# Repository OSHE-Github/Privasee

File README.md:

# Privasee

There are multiple different types of cameras. Detecting with them can be done in a combination of different ways. Some of these way include, but are not limited too detecting the infrared light pulses, reading the Radio Frequency and a handful of other waysPrivasee is a two semester project intended to locate and detect cameras. Additionally, the device itself aims to be low-cost, mobile, and efficient for detection. In other words, the device should be able to scan an area such as a hotel room and indicate to the user if there is a hidden camera. The basis of what to detect for hidden cameras boils down to infrared, radio frequencies, and possibly mac addresses. Infrared is a common trait of hidden cameras since this allows cameras to operate and record in low visibility. Radio frequency is used by hidden cameras to transmit data back to the owner. Mac addresses involve picking up packets sent in the area and displaying the signal strength and address of the device.

# Current State

The current prototype includes:
  
  - IR Detection
  - Mac Adress Reading 
  - RF detection (?)

  The system operates as a standalone or works with a laptop to detect cameras
  
# Features
## Infared Detection

Many imaging and sensing systems make use of infrared (IR) light for active detection. While standard full-color cameras rely on visible light, some systems emit IR pulses and measure their reflection to detect objects or changes in the environment. Other systems, such as thermal imaging, instead detect existing heat sources and do not require emitted signals.

This circuit focuses on detecting active IR pulses from an external source.

Using the logic shown in the diagram above, the system monitors for the presence of an incoming IR signal and responds when a valid pulse is detected.

The circuit below implements this detection mechanism. An IR sensor (photodiode or phototransistor) converts incoming infrared light into an electrical signal. This signal is then conditioned and amplified so it can be evaluated against a threshold.\

When the detected signal exceeds this threshold:
  - The circuit switches states
  - A control response is triggered
  - A buzzer is activated to indicate detection

This design allows the system to reliably detect IR pulses and convert them into a clear, real-time output signal. When integrated with a larger control loop, it can be used as an input for more complex sensing or decision-making systems.

## Radio Frequency
  Radio Frequency (RF) was chosen due to increasing amount of cameras connecting to Wifi. While connected to WiFi, cameras can capture vidoo and trasmit it. This makes it detectable for as it 
  emits oscilalitng EWF waves that can be picked up. For this semester of the project, the prototype aims to target active cameras transmitting over 2.4GHz.

### Antenna
  In order to start detecting signal a proper antenna is needed. The antenna will be responsible for picking up wifi signals that devices emit. In this case, the antenna must tuned to a
  resonance frequency of 2.4GHz. With proper tuning, the antenna will pick up these wifi signals more efficiently and this will result in a higher AC voltage.

### Diode Rectification
  Achieving high AC voltage make it much easier to amplify and notice difference in detection. A limiting factor of this AC voltage is that it is operating at 2.4GHz which is much more than
  what the LM358 can support. To amend this, a BAT41 diode was used to help rectify the AC voltage into DC voltage. Advantages of this include readable and processable voltage by the Op amp.
  Downsides of this diode involve voltage drops which results in a weaker signal. A capacitor and resistor is needed in parallel with the rectified diode voltage output in order to “hold” the
  DC voltage so it can be amplified by the OP Amp.

### Amplfication
  As mentioned earlier, amplification is needed to help create a more readable voltage. This it utilizing an LM358 Op amp in a non-inverting configuration. 

## MAC Address Reading
Many hidden cameras will connect to the internet to upload the videos/pictures they capture. The ESP32's built in WiFi Promiscuous mode can be used to capture packet information and do further analysis on packets in the area. This system only uses information available in IEEE 802.11 packet headers, such as the sending MAC address and data segment length. The ESP32 will also take an RSSI (Received Signal Strength Indicator) measurement when the packet is received. This data helps seperate each packet by a unique device identifier, and enables tracking of the changing signal stregth over time.
The ESP is unable to differentiate between device types by using this information, limiting this features ability to identify hidden cameras. Though this is the case, the MAC addresses and RSSI can be used to located devices in the area that are connected to the internet. 

# Tools Used

### Software
  Arduino IDE  
  Python  
  KiCad  
  OnShape  
  Git Desktop  

### Hardware
  Solder Iron Station  
  Wire Cutters  
  Wire Crimpers  

# Assembly Instructions

## RF

### Antenna
The SMA mount will be used as basis for the ground plane
Cut two lengths of copper wire to 33mm  
Cut longer than intended length adjustments/tuning can be made afterwords  
Solder one length of the copper wire to the signal pin forming a 90 degree angle  
Solder another length to the SMA mount leg pointing in the opposite direction of the signal pin  

### Board Assembly
Using the schematic for RF assemble the parts on to the protoboard  
Minimize amount of solder used components connecting into V+  
This includes the antenna, BAT41 diode, 1nF capacitor, 1Mohm resistor, and LM358 Op amp  

# Other catagories

### RF Flaws
A big issue with the RF side of this project revolved around a poor testing environment. The testing environment of RF was near an oscilloscope scope which constantly emitted EMF waves. These radiating waves from the oscilloscope cause the antenna on the breadboard to pick up a much stronger signal that what was expected on a 2.4ghz band. This error was caught later on in the semester and resulted in a more rushed prototype of what is currently featured above. While the concept of RF detection is proved, there are underdeveloped areas of RF which include antenna creation and op amp gain. Additionally factors such as parasitic capacitance and type of boards used were not analyzed as well.

The current graph shows some post error data of the current prototype. While this does display a correlation of RF being detected, the gain actual gain is really low. This is mainly due to the BAT41 diode used which did rectify the voltage but resulted in a 0.3V drop. Due to passive antennas not outputting much voltage, there was not a large amount of rectified voltage to be amplified by the op amp. 

#Appendex
- [Bill of Materials (BOM)](Documentation/BOM.md)

# Refrences
[1] “IR cameras - how they work and how to use them,” Sensorland.com, 2026. https://www.sensorland.com/HowPage105.html (accessed Apr. 20, 2026).

‌

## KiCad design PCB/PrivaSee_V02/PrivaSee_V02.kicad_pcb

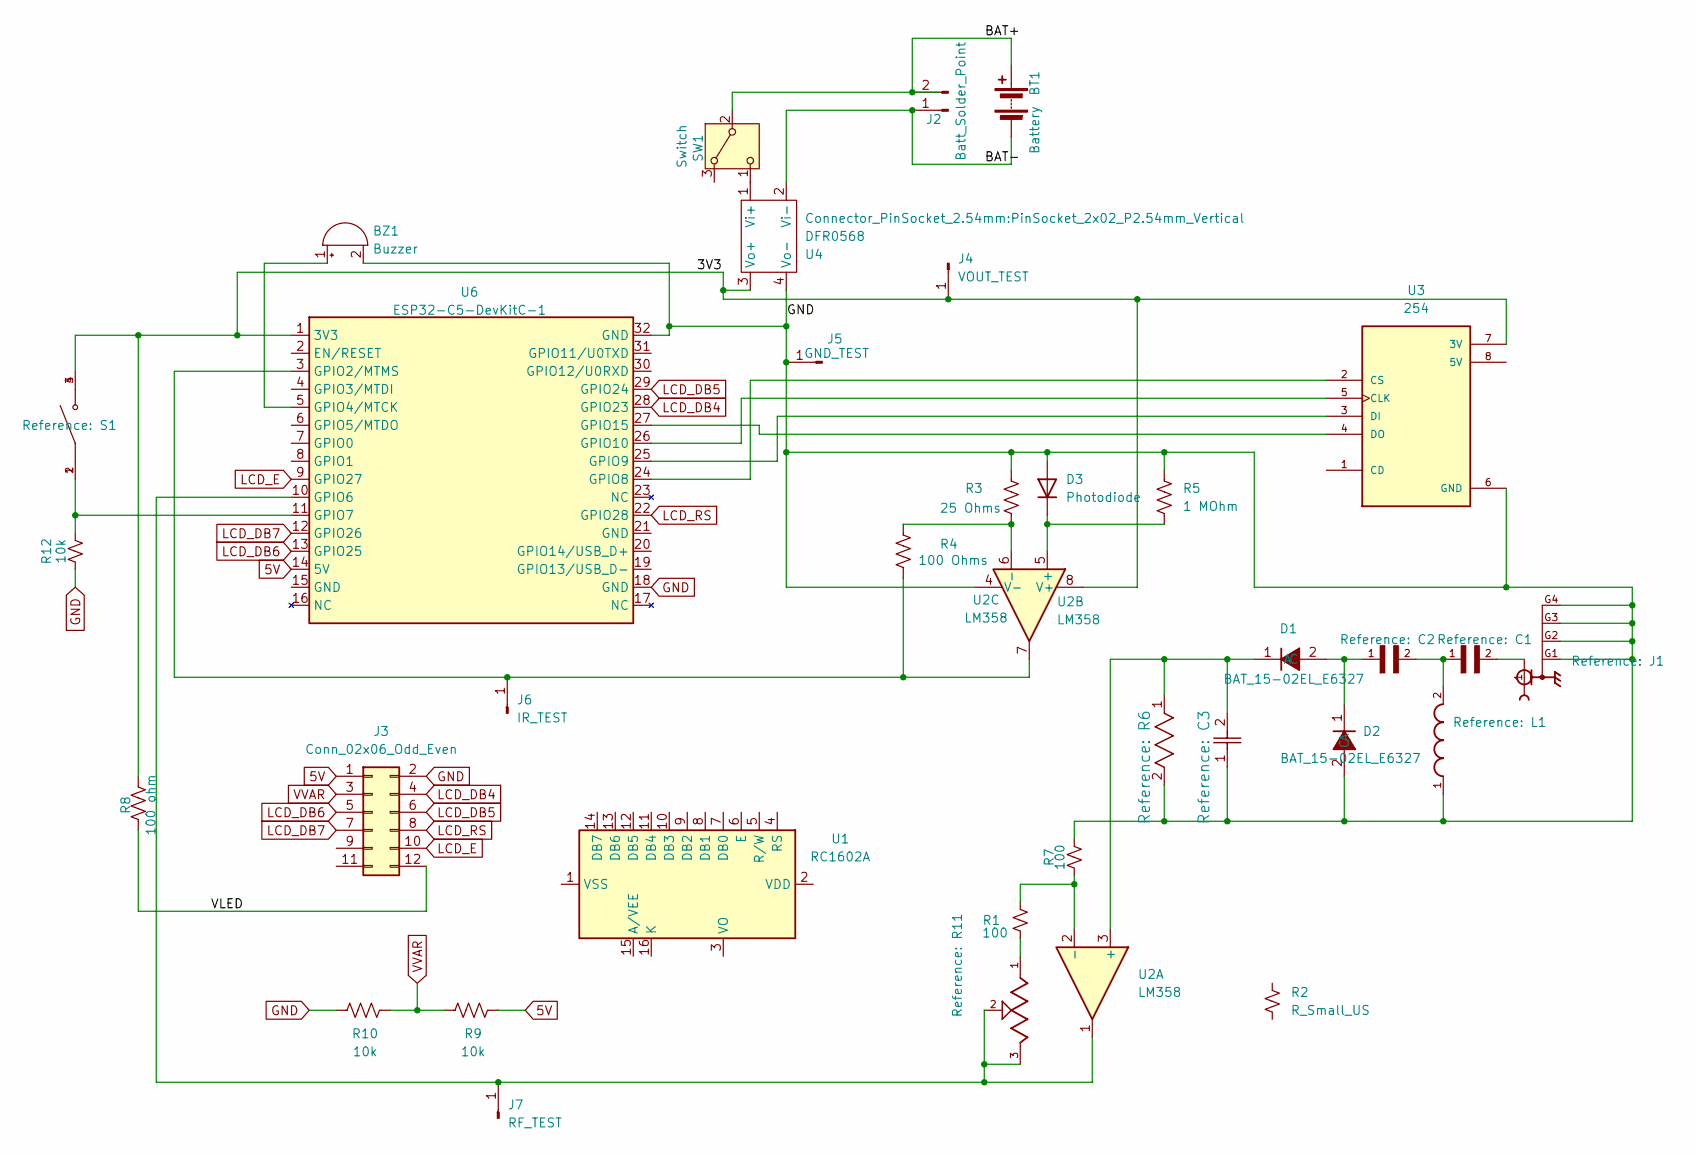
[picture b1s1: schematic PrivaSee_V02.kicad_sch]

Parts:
BT1: Battery; BatteryHolder_Keystone_2462_2xAA
BZ1: Buzzer; Buzzer_15x7.5RM7.6
C1: GJM1555C1HR22BB01D; CAPC1005X55N
C2: GJM1555C1H4R7BB01D; CAPC1005X55N
C3: GJM1555C1H220FB01D; CAP_GJM1555C1H220FB01D_MUR-L
D1, D2: BAT_15-02EL_E6327; Manufacturer Part BAT1502ELE6327; LCSC C533619
D3: Photodiode; D_A-405_P2.54mm_Vertical_AnodeUp
J1: RFPC-SMA27-F; GRADCONN_RFPC-SMA27-F; PARTREV 1.0
J2: Batt_Solder_Point; PinHeader_1x02_P2.54mm_Vertical
J3: Conn_02x06_Odd_Even; PinHeader_2x06_P2.54mm_Vertical
J4: VOUT_TEST; TestPoint_Pad_1.0x1.0mm
J5: GND_TEST; TestPoint_Pad_1.0x1.0mm
J6: IR_TEST; TestPoint_THTPad_1.5x1.5mm_Drill0.7mm
J7: RF_TEST; TestPoint_THTPad_1.5x1.5mm_Drill0.7mm
L1: LQW15AN9N1H00D; INDC1006X60N
R1, R7: 100; R_1206_3216Metric_Pad1.30x1.75mm_HandSolder
R2: R_Small_US
R3: 25 Ohms; R_1206_3216Metric_Pad1.30x1.75mm_HandSolder
R4: 100 Ohms; R_1206_3216Metric_Pad1.30x1.75mm_HandSolder
R5: 1 MOhm; R_1206_3216Metric_Pad1.30x1.75mm_HandSolder
R6: RT0402BRE07100KL; RC0402N_YAG-L
R8: 100 ohm; R_1206_3216Metric_Pad1.30x1.75mm_HandSolder
R9, R10, R12: 10k; R_1206_3216Metric_Pad1.30x1.75mm_HandSolder
R11: 3310Y-001-103L; TRIM_3310Y-001-103L
S1: D6R90_F2_LFS; SW_D6R90_F2_LFS; PARTREV 21 Feb 22
SW1: Switch; Nidec_Copal_CAS-120A
U1: RC1602A
U2: LM358; DIP-8_W7.62mm_Socket
U3: 254; PinHeader_1x08_P2.54mm_Vertical; PARTREV Jul 31, 2013
U4: DFR0568; PinSocket_2x02_P2.54mm_Vertical
U6: ESP32-C5-DevKitC-1

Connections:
5V: J3.1, R9.2, U6.14 (5V)
/3V3: J4.1 (Pin_1_1), R8.1, S1.3, S1.4, U2.8 (V+), U3.7 (3V), U4.3 (Vo+), U6.1 (3V3)
/BAT+: BT1.1 (+), J2.2 (Batt+), SW1.2 (B)
/BAT-: BT1.2 (-), J2.1 (Batt-), U4.2 (Vi-)
/VLED: J3.12, R8.2
GND: BZ1.2 (-), C3.1, D2.2 (A), D3.2 (A), J1.G1, J1.G2, J1.G3, J1.G4, J3.2, J5.1 (Pin_1_1), L1.1, R3.1, R5.1, R6.2, R7.2, R10.1, R12.1, U2.4 (V-), U3.6 (GND), U4.4 (Vo-), U6.18 (GND), U6.32 (GND)
LCD_DB4: J3.4, U6.28 (GPIO23)
LCD_DB5: J3.6, U6.29 (GPIO24)
LCD_DB6: J3.5, U6.13 (GPIO25)
LCD_DB7: J3.7, U6.12 (GPIO26)
LCD_E: J3.10, U6.9 (GPIO27)
LCD_RS: J3.8, U6.22 (GPIO28)
unnamed: BZ1.1 (+), U6.5 (GPIO4/MTCK)
unnamed: C1.1, C2.2, L1.2
unnamed: C1.2, J1.1
unnamed: C2.1, D1.2 (A), D2.1 (C)
unnamed: C3.2, D1.1 (C), R6.1, U2.3 (+)
unnamed: D3.1 (K), R5.2, U2.5 (+)
unnamed: J6.1 (Pin_1_1), R4.2, U2.7, U6.3 (GPIO2/MTMS)
unnamed: J7.1 (Pin_1_1), R11.2, R11.3, U2.1, U6.10 (GPIO6)
unnamed: R1.1, R11.1
unnamed: SW1.1 (C), U4.1 (Vi+)
unnamed: R1.2, R7.1, U2.2 (-)
unnamed: R3.2, R4.1, U2.6 (-)
unnamed: U3.5 (CLK), U6.26 (GPIO10)
unnamed: U3.2 (CS), U6.24 (GPIO8)
unnamed: U3.3 (DI), U6.25 (GPIO9)
unnamed: U3.4 (DO), U6.27 (GPIO15)
unnamed: R12.2, S1.1, S1.2, U6.11 (GPIO7)
VVAR: J3.3, R9.1, R10.2

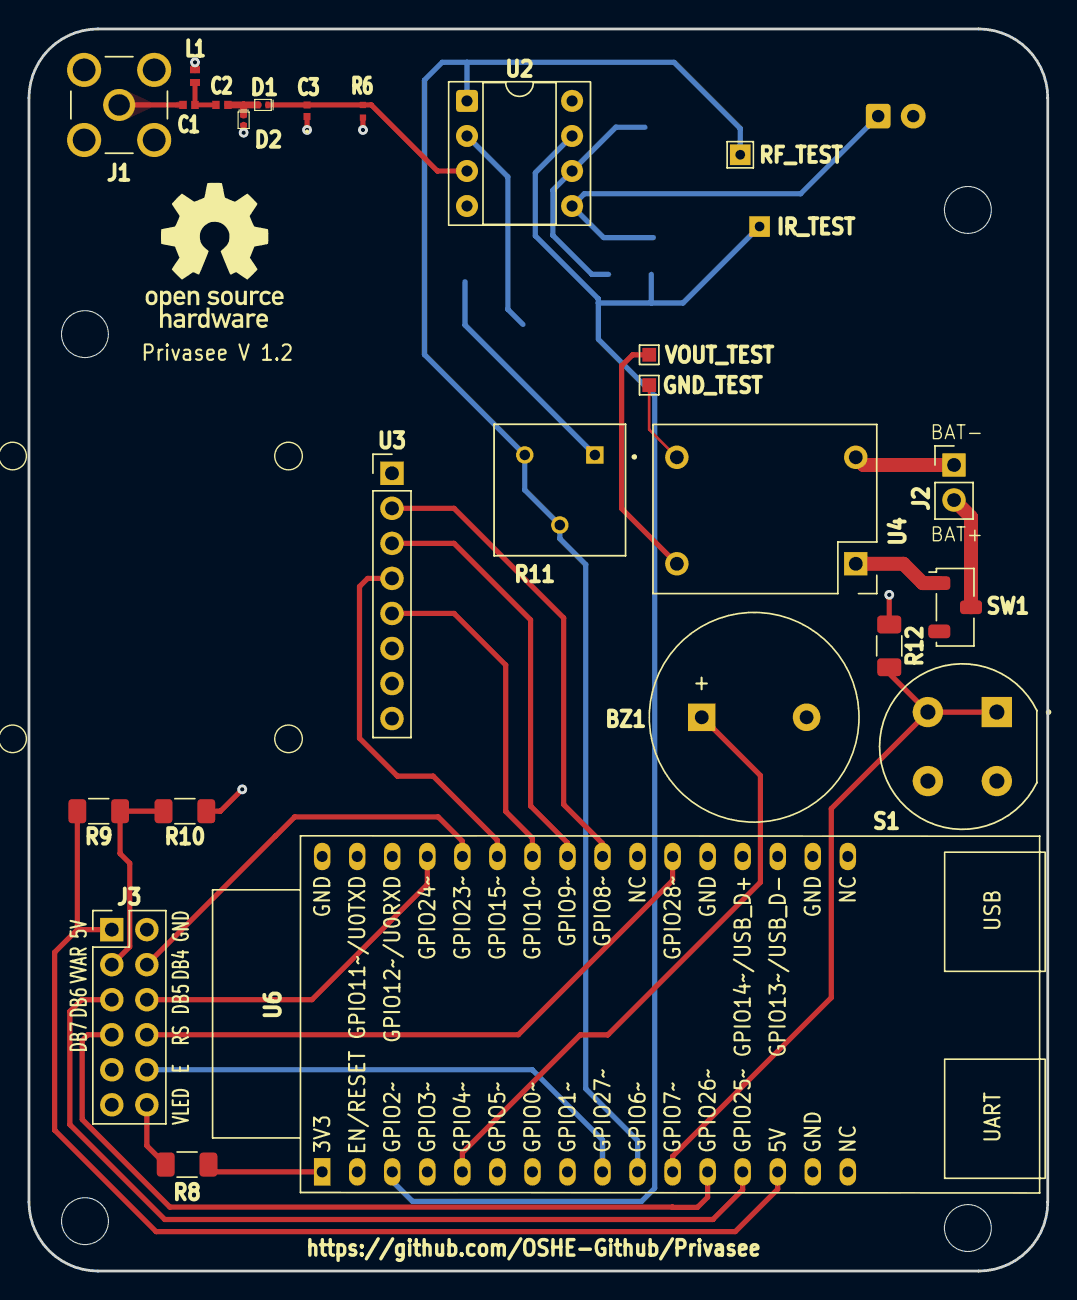
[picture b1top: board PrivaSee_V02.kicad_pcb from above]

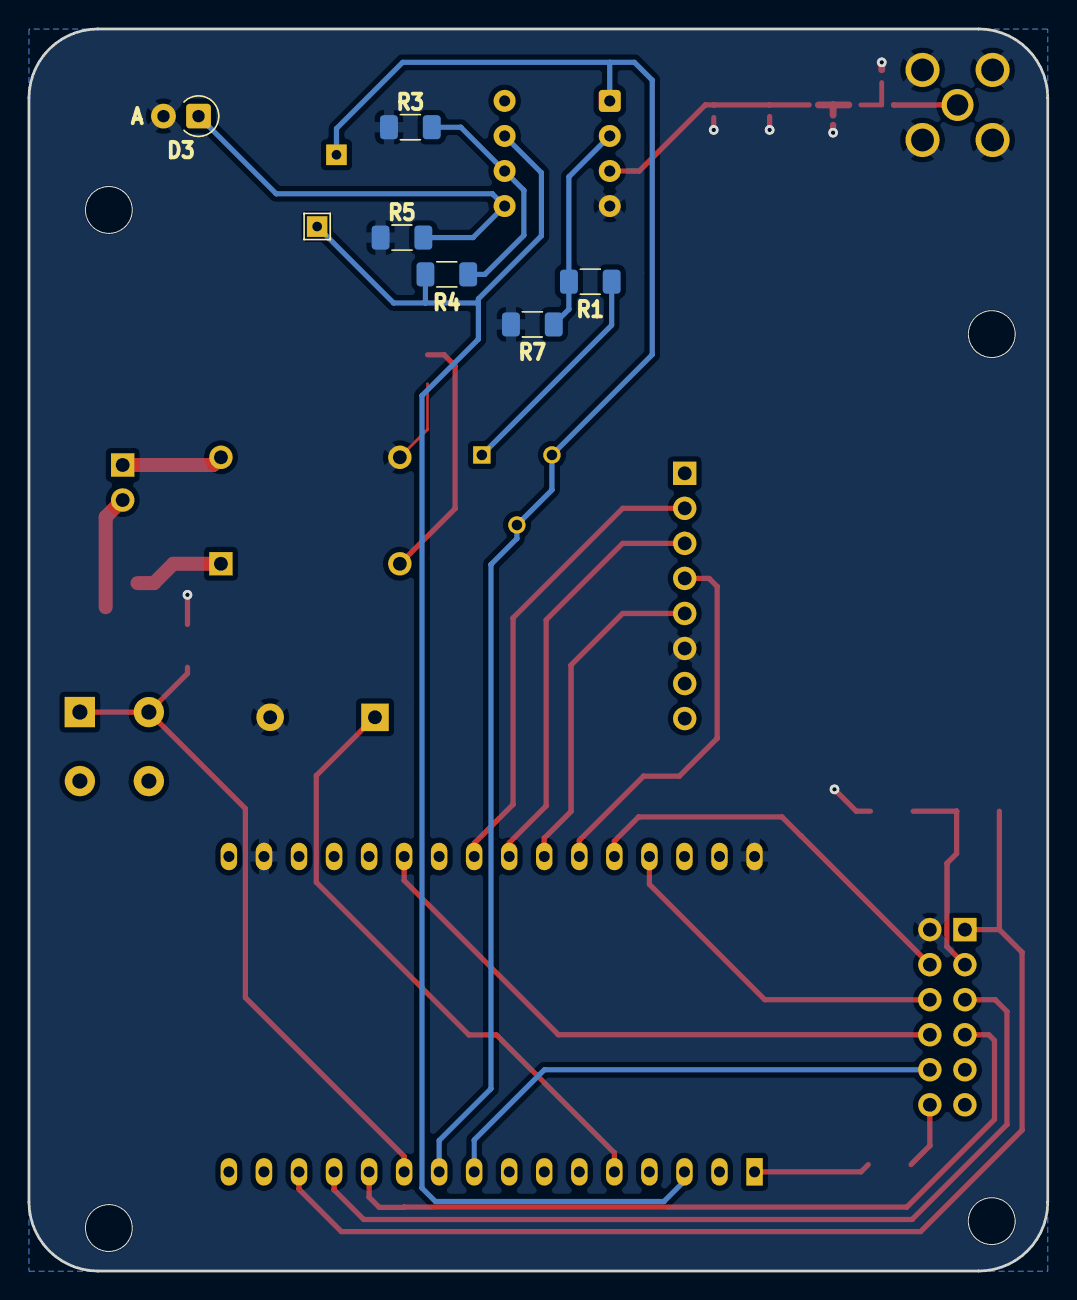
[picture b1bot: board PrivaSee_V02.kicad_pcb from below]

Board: 4 copper layers, 73.8 x 90.0 mm, 32 parts (7 on the bottom side), 30 nets.

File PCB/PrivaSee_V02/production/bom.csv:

Designator,Footprint,Quantity,Value,LCSC Part #
BZ1,Buzzer_15x7.5RM7.6,1,Buzzer,
C1,CAPC1005X55N,1,GJM1555C1HR22BB01D,
C2,G-155_MUR-L,1,GJM1555C1H4R7CB01D,
C3,CAP_GJM1555C1H220FB01D_MUR-L,1,GJM1555C1H220FB01D,
D1,BAT1504WH6327XTSA1,1,BAT1504WH6327XTSA1,C5380972
D3,D_A-405_P2.54mm_Vertical_AnodeUp,1,Photodiode,
J1,GRADCONN_RFPC-SMA27-F,1,RFPC-SMA27-F,
J2,PinHeader_1x02_P2.54mm_Vertical,1,Batt_Solder_Point,
J3,PinHeader_2x06_P2.54mm_Vertical,1,Conn_02x06_Odd_Even,
J4,TestPoint_Pad_1.0x1.0mm,1,VOUT_TEST,
J5,TestPoint_Pad_1.0x1.0mm,1,GND_TEST,
J6,TestPoint_THTPad_1.5x1.5mm_Drill0.7mm,1,IR_TEST,
J7,TestPoint_THTPad_1.5x1.5mm_Drill0.7mm,1,RF_TEST,
L1,INDC1006X60N,1,LQW15AN9N1H00D,
R1,1206,1,200,
"R10, R12, R9",1206,3,10k,
R2,1206,1,470 Ohm,
R3,1206,1,25 Ohms,
R4,1206,1,100 Ohms,
R5,1206,1,1 MOhm,
R6,RC0402N_YAG-L,1,RT0402BRE07100KL,
R7,1206,1,10,
R8,1206,1,100 ohm,
SW1,Nidec_Copal_CAS-120A,1,Switch,
SW2,SW_PUSH_6mm_H4.3mm,1,SW_Push,
U2,DIP-8_W7.62mm_Socket,1,LM358,
U3,PinHeader_1x08_P2.54mm_Vertical,1,254,
U4,PinSocket_2x02_P2.54mm_Vertical,1,DFR0568,
U5,ESP32-C6-DevKitC-1,1,ESP32-C6-DevKitC-1,

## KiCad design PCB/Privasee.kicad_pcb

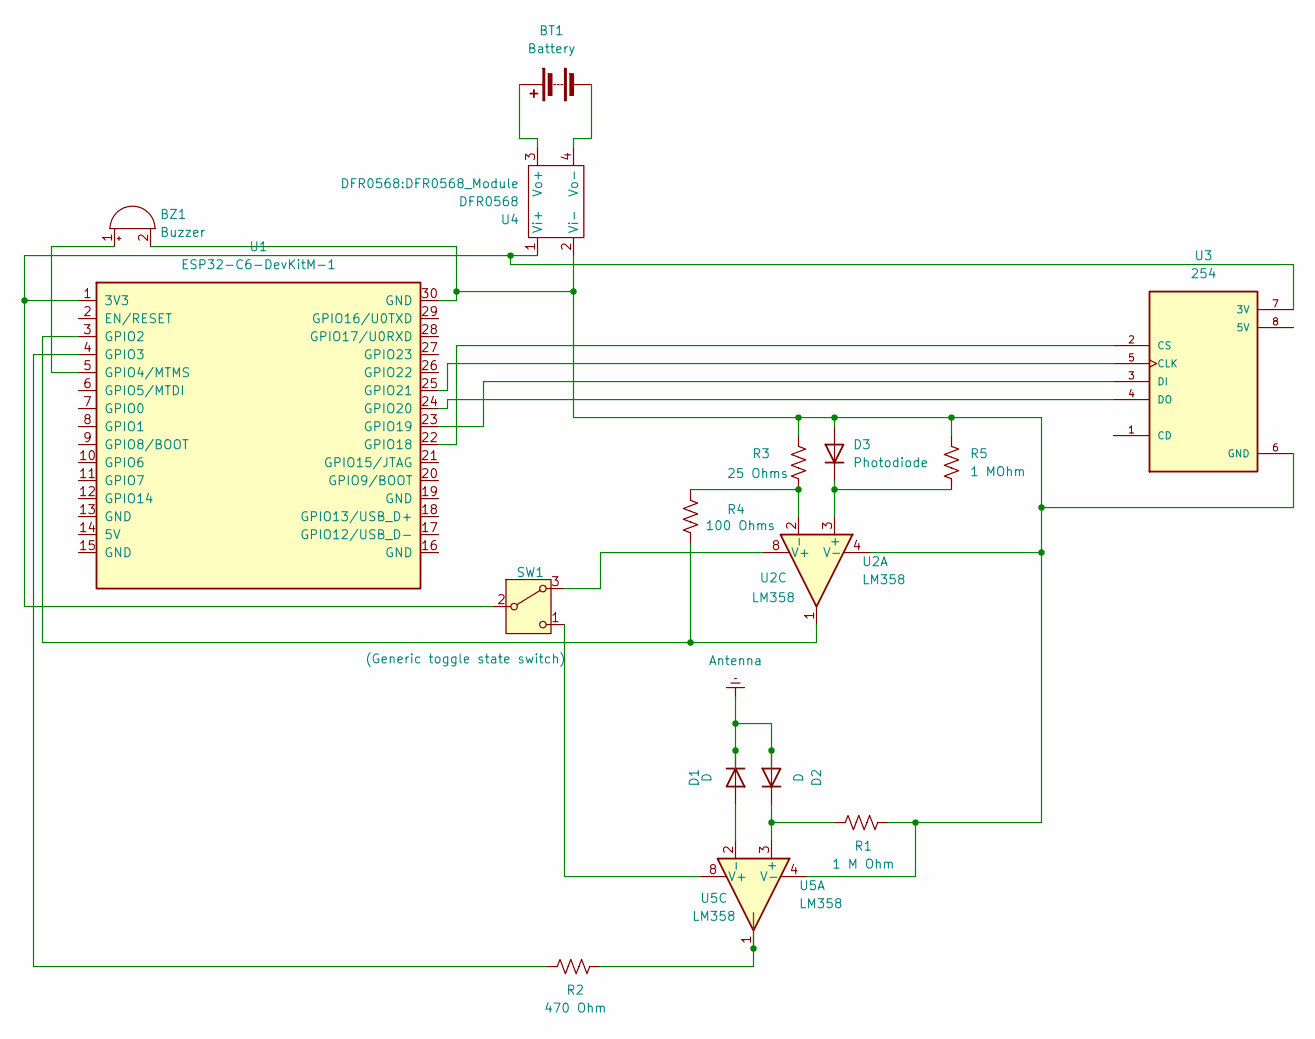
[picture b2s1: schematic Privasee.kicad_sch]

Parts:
BT1: Battery; BatteryHolder_Keystone_2462_2xAA
BZ1: Buzzer; Buzzer_15x7.5RM7.6
D1, D2: D; D_5KPW_P7.62mm_Vertical_AnodeUp
D3: Photodiode; D_SOD-523
R1: 1 M Ohm; R_Array_SIP4
R2: 470 Ohm; R_Array_SIP4
R3: 25 Ohms; R_Array_SIP4
R4: 100 Ohms; R_Array_SIP4
R5: 1 MOhm; R_Array_SIP4
SW1: (Generic toggle state switch); Nidec_Copal_CAS-120A
U1: ESP32-C6-DevKitM-1
U2, U5: LM358; DIP-8_W7.62mm
U3: 254; MODULE_254; PARTREV Jul 31, 2013
U4: DFR0568; DFR0568_Module

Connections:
Antenna: D1.1 (K), D2.2 (A)
unnamed: BT1.1 (+), U4.3 (Vo+)
unnamed: BT1.2 (-), U4.4 (Vo-)
unnamed: BZ1.1 (+), U1.5 (GPIO4/MTMS)
unnamed: BZ1.2 (-), D3.2 (A), R1.2, R3.1, R5.1, U1.30 (GND), U2.4 (V-), U3.6 (GND), U4.2 (Vi-), U5.4 (V-)
unnamed: D1.2 (A), U5.2 (-)
unnamed: D2.1 (K), R1.1, U5.3 (+)
unnamed: D3.1 (K), R5.2, U2.3 (+)
unnamed: R2.2, U5.1
unnamed: SW1.3 (A), U2.8 (V+)
unnamed: SW1.2 (B), U1.1 (3V3), U3.7 (3V), U4.1 (Vi+)
unnamed: SW1.1 (C), U5.8 (V+)
unnamed: R4.2, U1.3 (GPIO2), U2.1
unnamed: R2.1, U1.4 (GPIO3)
unnamed: U1.22 (GPIO18), U3.2 (CS)
unnamed: U1.23 (GPIO19), U3.3 (DI)
unnamed: U1.24 (GPIO20), U3.4 (DO)
unnamed: U1.25 (GPIO21), U3.5 (CLK)
unnamed: R3.2, R4.1, U2.2 (-)

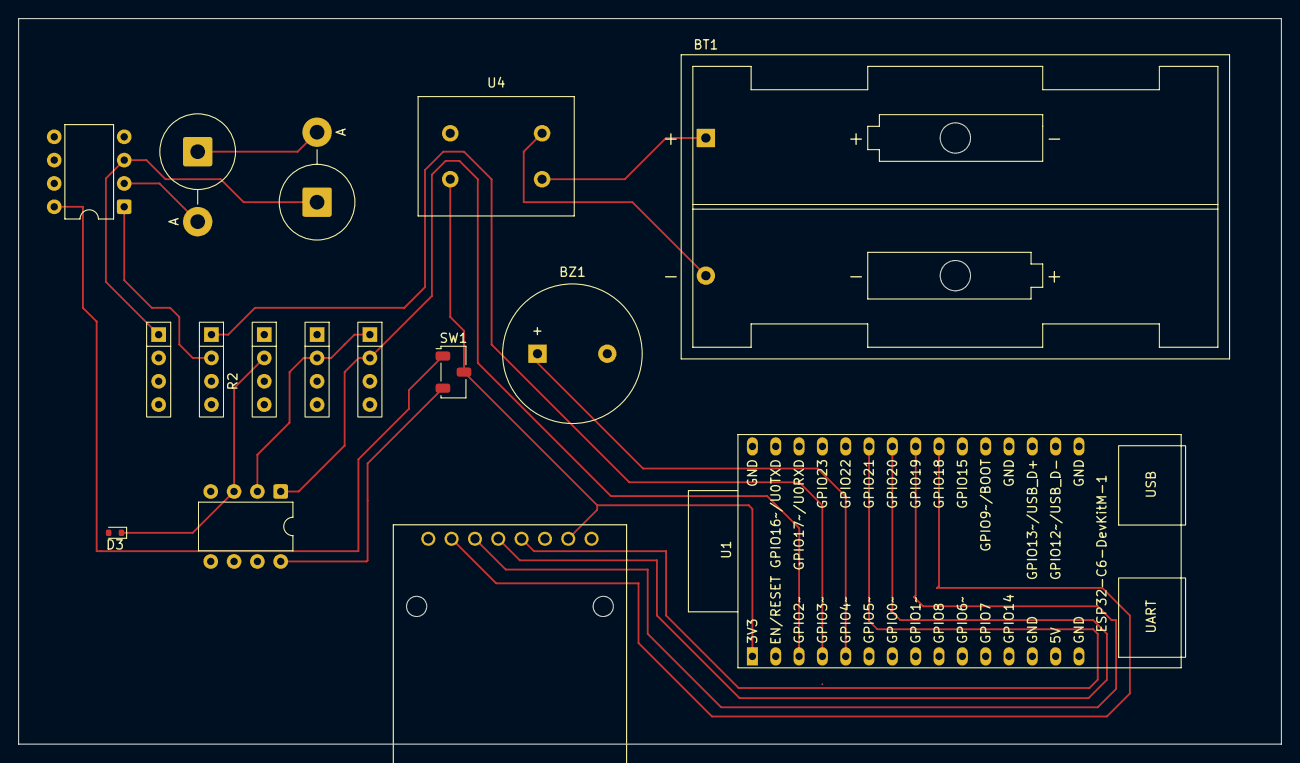
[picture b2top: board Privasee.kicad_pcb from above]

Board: 2 copper layers, 137.5 x 79.0 mm, 16 parts (0 on the bottom side), 19 nets.

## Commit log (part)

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2026-03-27 Create ir.ino
    Updated code as of 3/27/26 for IR. preparing for SD card logging & merging with at least mac address trackign
2026-03-27 Update README.md
    Brief project description
2026-03-27 Case for breadboard prototype
    Case F
2026-03-27 Rename Part Studio 1 - Part 1.stl to Magnfine_wave_amplifier.stl
2026-03-27 Rename Part Studio 1 - Part 1(1).stl to Breadboard_case.stl
2026-03-27 Create a
2026-03-27 Rename Breadboard_case.stl to hardware/Breadboard_case.stl
2026-03-27 Rename Magnfine_wave_amplifier.stl to hardware/Magnfine_wave_amplifier.stl
2026-03-27 Rename ir.ino to firmware/ir.ino
2026-03-29 Rename Privaseer.kicad_sch to PCB/Privaseer.kicad_sch
2026-04-01 Update mainbioard.ino
    IR + Wifi packets logic merged
2026-04-01 Rename full_test.csv to data/full_test.csv
2026-04-01 Rename plotter.py to data/plotter.py
2026-04-01 fixed arduino project structure
2026-04-01 more project reformatting
2026-04-01 print packet function
2026-04-01 added packet logging
2026-04-01 cleaned up debug messages
2026-04-01 remove delay
2026-04-01 disabled packet logging in the IR log
2026-04-16 Update README.md
    testing
2026-04-17 RF Features README.md
2026-04-17 Features + Schematic README.md
2026-04-17 Figures README.md
2026-04-17 BOM Test README.md
2026-04-17 RF BOM README.md
2026-04-17 RF Flaws README.md
2026-04-17 Tools Adjustment README.md
2026-04-17 RF Assembly README.md
2026-04-17 Spacing Adjustments README.md
2026-04-21 mac addr reading
